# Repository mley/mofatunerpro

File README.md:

# MofaTunerPro

Arduino + Android project for my brother's race bike. The arduino reads throttle 
position, RPM and lambda value and transmits this data via bluetooth to the 
android app. The app displays and logs the data. The data shall give advice how 
to setup the carburetor for optimal performance.

Work in progress. Photos, schematics coming soon.

## Acknowledgements
* Kostas Kokoras for his inductive spark plug sensor circuit design and arduino code
  https://kokoraskostas.blogspot.co.at/2013/12/arduino-inductive-spark-plug-sensor.html
* Sebastian Knödler for his wideband lambda sensor kit 
  http://www.breitband-lambda.de/produkte.html
* Philipp Jahoda for his Android graph library MPAndroidChart
  https://github.com/PhilJay/MPAndroidChart

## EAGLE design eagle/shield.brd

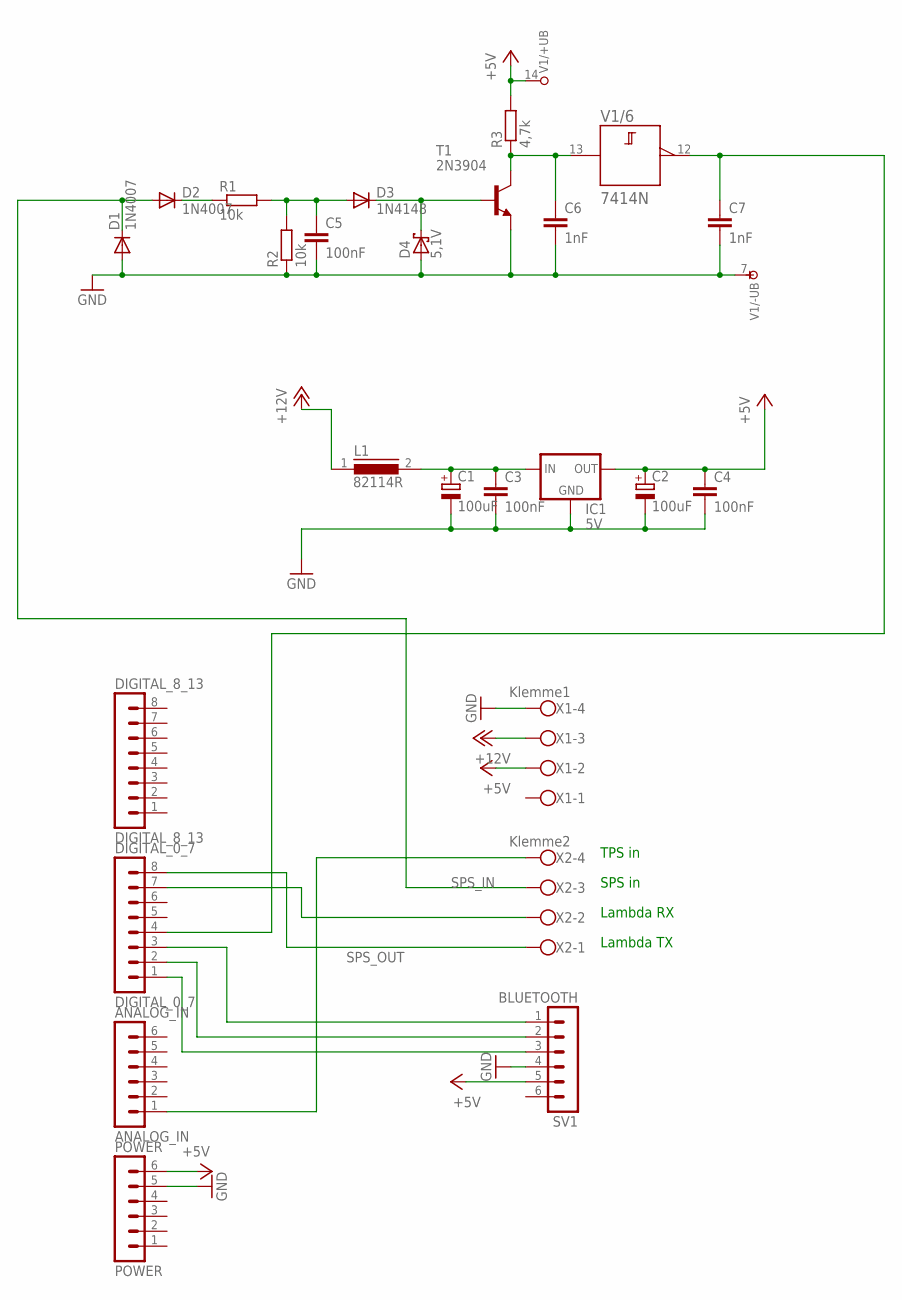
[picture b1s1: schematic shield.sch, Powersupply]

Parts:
ANALOG_IN: ANALOG_IN; MA06-1
C1, C2: 100uF; E2-4
C3, C4: 100nF; C050-035X075
C5: 100nF; C075-032X103
C6, C7: 1nF; C075-032X103
D1, D2: 1N4007; D-5
D3: 1N4148; D-5
D4: 5,1V; DO35-7
DIGITAL_0_7: DIGITAL_0_7; MA08-1
DIGITAL_8_13: DIGITAL_8_13; MA08-1
IC1: 5V; 78XXS
L1: 82114R
POWER: POWER; MA06-1
R1, R2: 10k; 0204/5
R3: 4,7k; 0204/5
SV1: BLUETOOTH; MA06-1
T1: 2N3904; TO92
V1: 7414N; DIL14
X1: Klemme1; W237-4
X2: Klemme2; W237-4

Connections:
+5V: C2.+, C4.1, IC1.OUT, POWER.6, R3.2, SV1.5, V1.14 (+UB), X1.2
+12V: L1.1, X1.3
GND: C1.-, C2.-, C3.2, C4.2, C5.2, C6.2, C7.2, D1.A, D4.A, IC1.GND, POWER.5, R2.1, SV1.4, T1.3 (E), V1.7 (-UB), X1.4
unnamed: C1.+, C3.1, IC1.IN, L1.2
unnamed: DIGITAL_0_7.7, X2.2
unnamed: DIGITAL_0_7.8, X2.1
unnamed: D2.C, R1.1
unnamed: C5.1, D3.A, R1.2, R2.2
unnamed: D3.C, D4.C, T1.2 (B)
unnamed: C6.1, R3.1, T1.1 (C), V1.13 (A)
unnamed: ANALOG_IN.1, X2.4
unnamed: DIGITAL_0_7.2, SV1.2
unnamed: DIGITAL_0_7.1, SV1.3
unnamed: DIGITAL_0_7.3, SV1.1
SPS_IN: D1.C, D2.A, X2.3
SPS_OUT: C7.1, DIGITAL_0_7.4, V1.12 (Y)

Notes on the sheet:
TPS in
SPS in
Lambda RX
Lambda TX

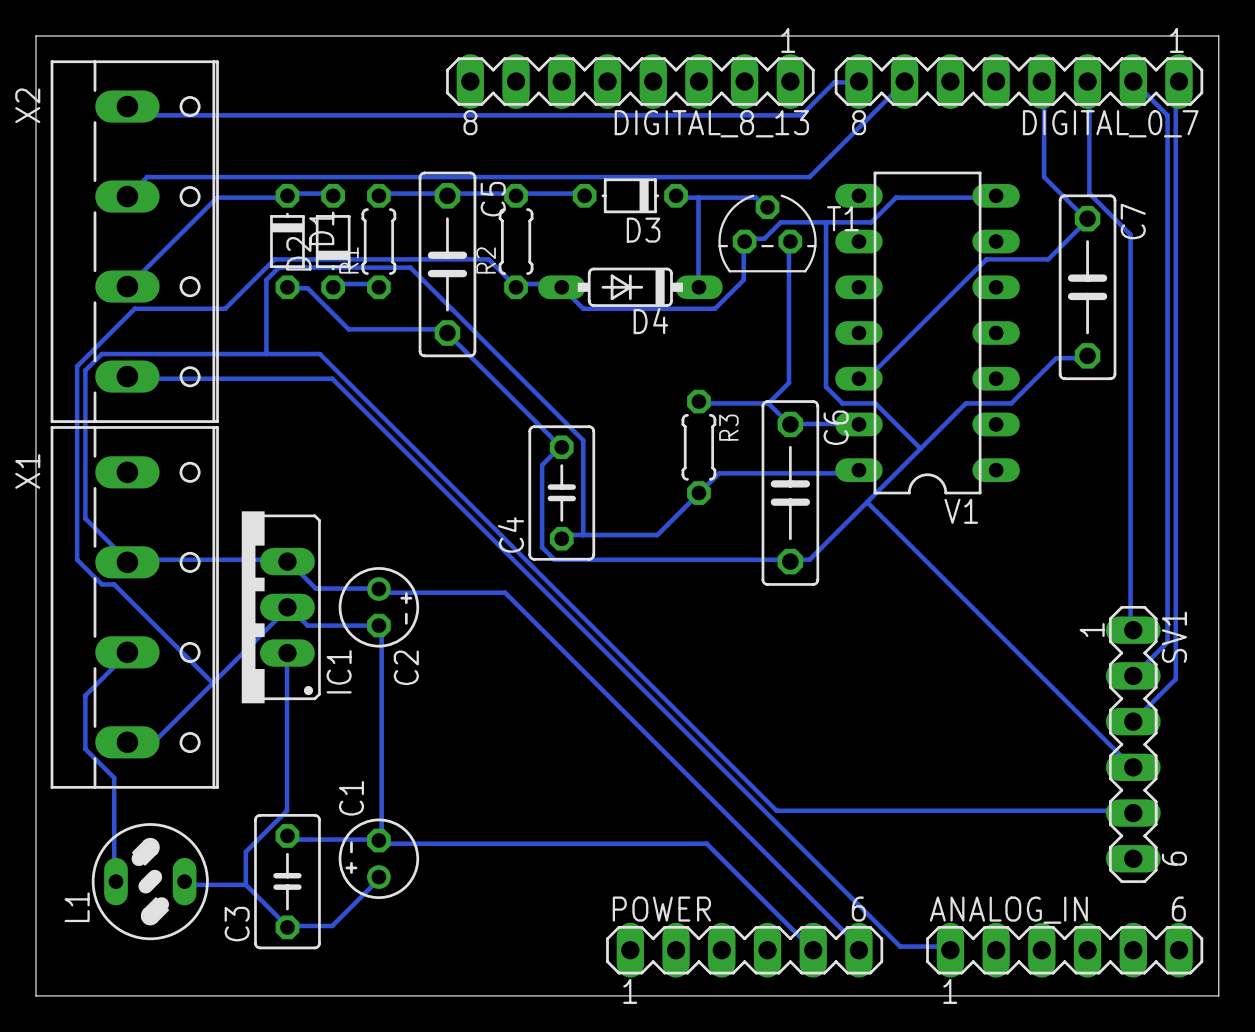
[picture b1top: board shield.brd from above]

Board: 2 copper layers, 65.7 x 53.3 mm, 25 parts (0 on the bottom side), 16 nets.

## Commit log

2016-06-18 more readme
2016-06-18 removed generated comments, readme
2016-09-12 Added eagle schematics and PCB
